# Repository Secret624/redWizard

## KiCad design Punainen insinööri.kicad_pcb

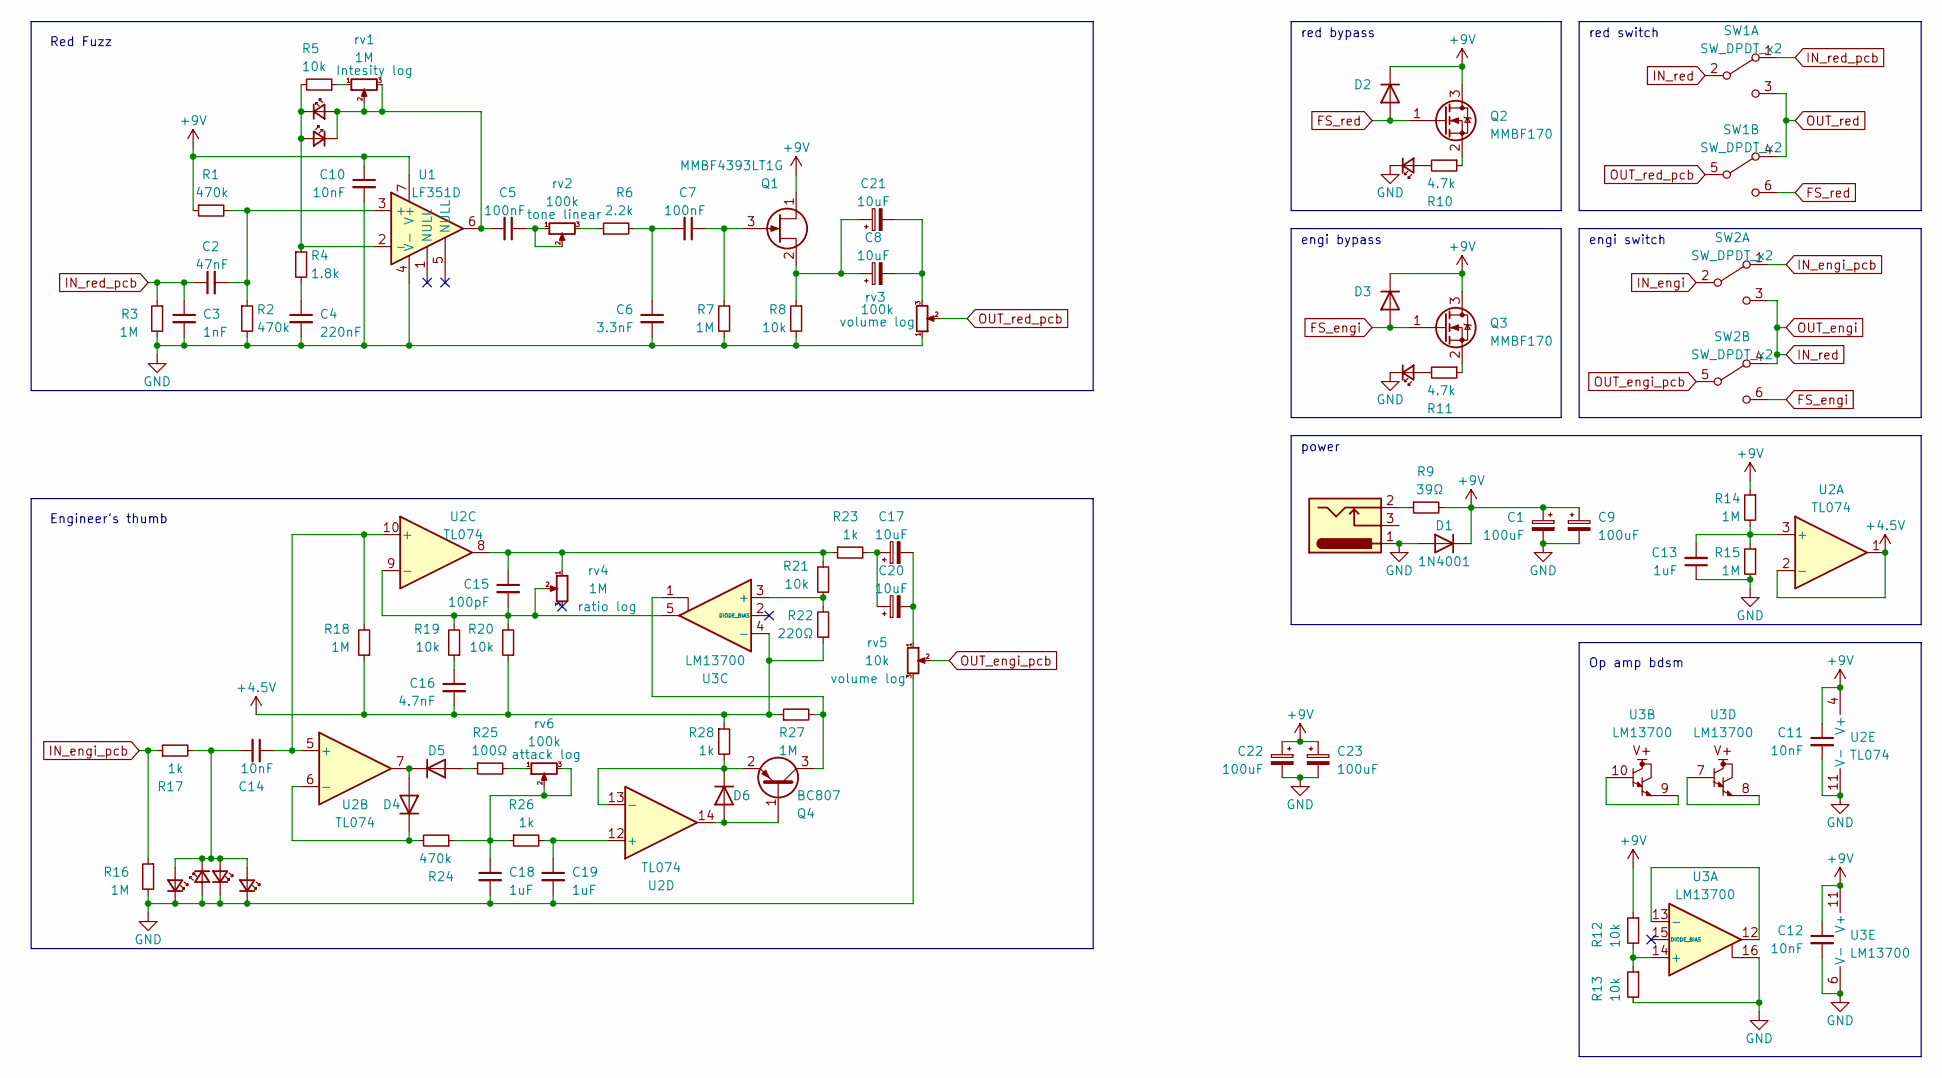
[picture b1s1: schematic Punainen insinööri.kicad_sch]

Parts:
C1, C9, C22, C23: 100uF; CP_Elec_6.3x5.4; LCSC# C37308
C2: 47nF; C_0805_2012Metric_Pad1.18x1.45mm_HandSolder; LCSC# C520039
C3: 1nF; C_0805_2012Metric_Pad1.18x1.45mm_HandSolder; LCSC# C376859
C4: 220nF; C_0805_2012Metric_Pad1.18x1.45mm_HandSolder; LCSC# C541526
C5, C7: 100nF; C_0805_2012Metric_Pad1.18x1.45mm_HandSolder; LCSC# C282730
C6: 3.3nF; C_0805_2012Metric_Pad1.18x1.45mm_HandSolder; LCSC# C1322372
C8, C17, C20, C21: 10uF; CP_Elec_4x5.4; LCSC# C4747969
C10, C11, C12, C14: 10nF; C_0805_2012Metric_Pad1.18x1.45mm_HandSolder; LCSC# C58456
C13, C18, C19: 1uF; C_0805_2012Metric_Pad1.18x1.45mm_HandSolder; LCSC# C520051
C15: 100pF; C_0805_2012Metric_Pad1.18x1.45mm_HandSolder; LCSC# C525281
C16: 4.7nF; C_0805_2012Metric_Pad1.18x1.45mm_HandSolder; LCSC# C376986
D1: 1N4001; D_SOD-123F; LCSC# C2892326
D2, D3, D4, D5, D6: 1N4148W; D_SOD-123; LCSC# C5345962
J1: Barrel_Jack_Switch; BarrelJack_Horizontal; LCSC# C194407
LED1, LED2, LED5, LED6: LED_Small; LED_1206_3216Metric_Pad1.42x1.75mm_HandSolder; LCSC# C84263
LED3, LED4: LED_Small
LED7: LED_Small; LED_D3.0mm; LCSC# C84263
LED8: LED_Small; LED_D3.0mm
Q1: MMBF4393LT1G; SOT-23; LCSC# C152291
Q2, Q3: MMBF170; SOT-23; LCSC# C5330373
Q4: BC807; SOT-23; LCSC# C5184433
R1, R2, R24: 470k; R_0805_2012Metric_Pad1.20x1.40mm_HandSolder; LCSC# C2960743
R3, R7, R14, R15, R16, R18, R27: 1M; R_0805_2012Metric_Pad1.20x1.40mm_HandSolder; LCSC# C103906
R4: 1.8k; R_0805_2012Metric_Pad1.20x1.40mm_HandSolder; LCSC# C17398
R5, R8, R12, R13, R19, R20, R21: 10k; R_0805_2012Metric_Pad1.20x1.40mm_HandSolder; LCSC# C17414
R6: 2.2k; R_0805_2012Metric_Pad1.20x1.40mm_HandSolder; LCSC# C104106
R9: 39Ω; R_1206_3216Metric_Pad1.30x1.75mm_HandSolder; LCSC# C153384
R10, R11: 4.7k; R_0805_2012Metric_Pad1.20x1.40mm_HandSolder; LCSC# C2907264
R17, R23, R26, R28: 1k; R_0805_2012Metric_Pad1.20x1.40mm_HandSolder; LCSC# C2907232
R22: 220Ω; R_0805_2012Metric_Pad1.20x1.40mm_HandSolder; LCSC# C2933369
R25: 100Ω; R_1206_3216Metric_Pad1.30x1.75mm_HandSolder; LCSC# C3016626
SW1, SW2: SW_DPDT_x2; SW_Push_2P2T_Toggle_CK_PVA2xxH1xxxxxxV2
U1: LF351D; SO-8_3.9x4.9mm_P1.27mm; LCSC# C1346659
U2: TL074; SO-14_3.9x8.65mm_P1.27mm; LCSC# C107644
U3: LM13700; SOP-16_3.9x9.9mm_P1.27mm; LCSC# C5160094
rv1, rv4: 1M; Potentiometer redwiz
rv2, rv3, rv6: 100k; Potentiometer redwiz
rv5: 10k; Potentiometer redwiz

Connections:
+5V: C16.2, R18.1, R20.1, R22.1, R27.1, R28.1, U2.1, U2.2 (-), U3.4 (-)
+9V: C1.1, C9.1, C10.1, C11.1, C12.1, C22.1, C23.1, D1.1 (K), D2.1 (K), D3.1 (K), Q1.1 (D), Q2.3 (D), Q3.3 (D), R1.1, R9.2, R12.1, R14.1, U1.7 (V+), U2.4 (V+), U3.11 (V+)
FS_engi: D3.2 (A), Q3.1 (G), SW2.6 (C)
FS_red: D2.2 (A), Q2.1 (G), SW1.6 (C)
GND: C1.2, C3.2, C4.2, C6.2, C9.2, C10.2, C11.2, C12.2, C13.1, C18.2, C19.2, C22.2, C23.2, D1.2 (A), J1.1, LED3.1 (K), LED4.1 (K), LED5.2 (A), LED6.1 (K), LED7.1 (K), LED8.1 (K), R2.2, R3.2, R7.2, R8.2, R13.2, R15.2, R16.2, U1.4 (V-), U2.11 (V-), U3.6 (V-), U3.16, rv3.1, rv5.3; also elsewhere on the board
IN_engi_pcb: R16.1, R17.1, SW2.1 (A); also elsewhere on the board
IN_red_pcb: C2.1, C3.1, R3.1, SW1.1 (A); also elsewhere on the board
unnamed: C4.1, R4.2
unnamed: C5.1, rv2.1, rv2.2
unnamed: C6.1, C7.2, R6.2
unnamed: C15.1, R21.2, R23.1, U2.8, rv4.1
unnamed: C16.1, R19.1
unnamed: C17.1, C20.1, R23.2
unnamed: C17.2, C20.2, rv5.1
unnamed: C18.1, R24.1, R26.1, rv6.2, rv6.3
unnamed: C8.2, C21.2, rv3.3
unnamed: D4.2 (A), D5.1 (K), U2.7
unnamed: D4.1 (K), R24.2, U2.6 (-)
unnamed: D5.2 (A), R25.1
unnamed: D6.2 (A), Q4.1 (B), U2.14
unnamed: D6.1 (K), Q4.2 (E), R28.2, U2.13 (-)
unnamed: J1.2, R9.1
unnamed: C5.2, LED1.2 (A), LED2.1 (K), U1.6, rv1.2, rv1.3
unnamed: LED1.1 (K), LED2.2 (A), R4.1, R5.2, U1.2 (-)
unnamed: LED3.2 (A), R10.2
unnamed: LED4.2 (A), R11.2
unnamed: C14.2, LED5.1 (K), LED6.2 (A), LED7.2 (A), LED8.2 (A), R17.2
unnamed: C7.1, Q1.3 (G), R7.1
unnamed: C8.1, C21.1, Q1.2 (S), R8.1
unnamed: Q2.2 (S), R10.1
unnamed: Q3.2 (S), R11.1
unnamed: Q4.3 (C), R27.2, U3.1
unnamed: R5.1, rv1.1
unnamed: R6.1, rv2.3
unnamed: R25.2, rv6.1
unnamed: SW1.2 (B), SW2.3 (C), SW2.4 (A)
unnamed: SW1.3 (C), SW1.4 (A)
unnamed: C2.2, R1.2, R2.1, U1.3 (+)
unnamed: C13.2, R14.2, R15.1, U2.3 (+)
unnamed: C14.1, R18.2, U2.5 (+), U2.10 (+)
unnamed: C15.2, R19.2, R20.2, U2.9 (-), U3.5, rv4.2
unnamed: C19.1, R26.2, U2.12 (+)
unnamed: U3.7, U3.8
unnamed: U3.9, U3.10
unnamed: R12.2, R13.1, U3.14 (+)
unnamed: U3.12, U3.13 (-)
unnamed: R21.1, R22.2, U3.3 (+)
OUT_engi_pcb: SW2.5 (B), rv5.2; also elsewhere on the board
OUT_red_pcb: SW1.5 (B), rv3.2; also elsewhere on the board

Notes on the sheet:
red bypass
Op amp bdsm
engi switch
Red Fuzz
power
Engineer's thumb
engi bypass
red switch

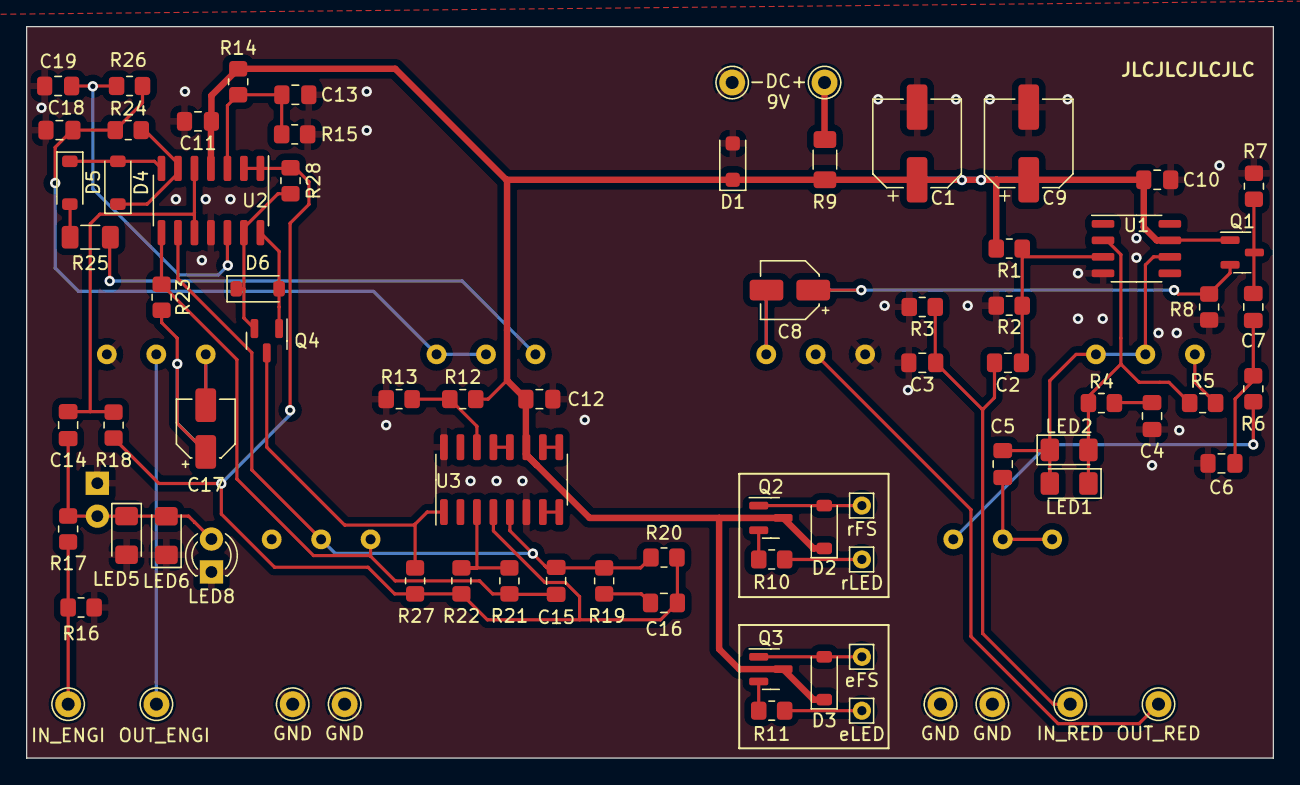
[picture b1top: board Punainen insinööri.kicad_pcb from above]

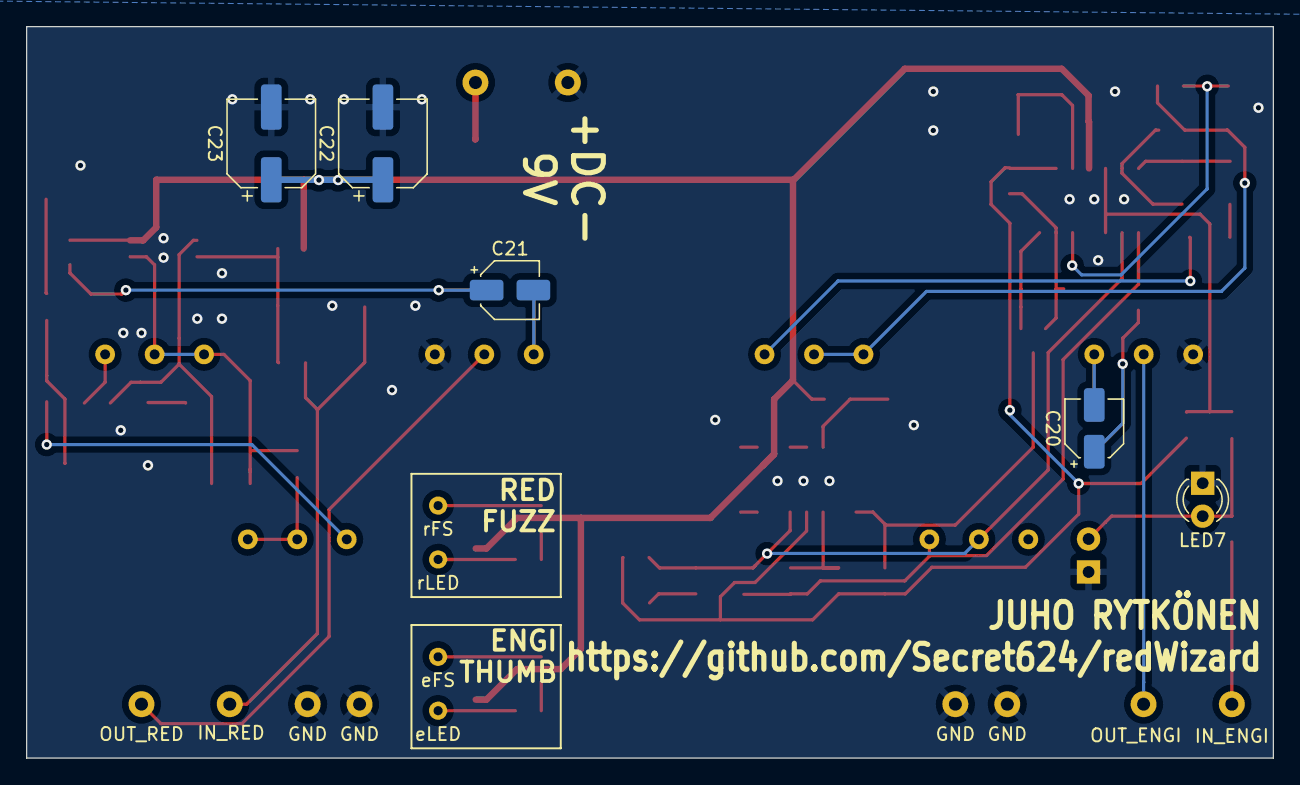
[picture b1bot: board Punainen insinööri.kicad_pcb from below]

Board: 2 copper layers, 96.0 x 56.3 mm, 84 parts (11 on the bottom side), 44 nets.

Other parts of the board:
GND: Pin_D1.0mm_L10.0mm
GND#2, GND#3, GND#4: Pin_D1.0mm_L10.0mm
IN_ENGI: Pin_D1.0mm_L10.0mm
IN_RED: Pin_D1.0mm_L10.0mm
OUT_ENGI: Pin_D1.0mm_L10.0mm
OUT_RED: Pin_D1.0mm_L10.0mm

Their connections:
GND: GND.1, GND#2.1, GND#3.1, GND#4.1; also elsewhere on the board
IN_engi_pcb: IN_ENGI.1; also elsewhere on the board
IN_red_pcb: IN_RED.1; also elsewhere on the board
OUT_engi_pcb: OUT_ENGI.1; also elsewhere on the board
OUT_red_pcb: OUT_RED.1; also elsewhere on the board

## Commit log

2023-09-01 genesis
2023-09-01 jotain säätöä
2023-09-01 the trans question
2023-09-02 small fixes
2023-09-02 millenials in shambles
2023-09-03 Schema valmiina
2023-09-04 pieniä muutoksia
2023-09-10 pcb v1
2023-09-10 pcb v1.1
2023-09-12 pcb v1.2
2023-09-15 Konkan tuplaus temppu
2023-09-15 Konkka temppu 2
2023-09-15 Ledin lisäys loitsu
